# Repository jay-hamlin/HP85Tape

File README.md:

PYTHON
 - command line: python3 hp85Main.py
 - edit hp85Uart.py with path of FTDI serial port.

FPGA
 - FPGA is Lattice iCE40HX1K-TQ144
 - Use Lattice ICEStick development board.
 - Editor is MS Visual Studio Code
 - Simulation with Mentor Graphics ModelSim "PE Student Edition"
 - Synthesis with LAttice iCECube2. Use Synplify Pro option.
 - Program FPGA with Lattice Diamond Programmer.

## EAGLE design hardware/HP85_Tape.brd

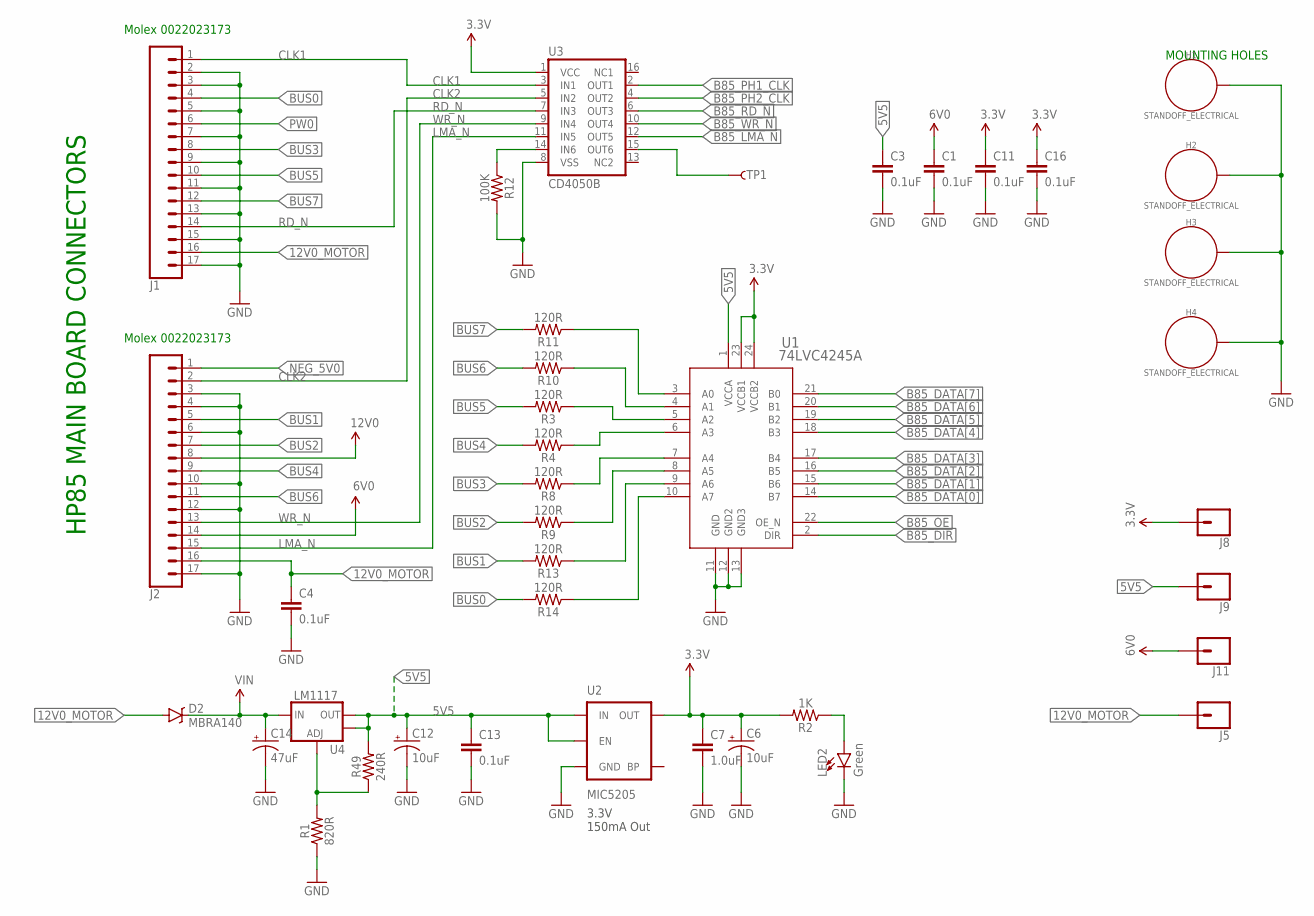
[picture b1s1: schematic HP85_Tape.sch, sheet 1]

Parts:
C1, C3, C4, C11, C13, C16: 0.1uF; 0603
C6, C12: 10uF; EIA3216
C7: 1.0uF; 0603
C14: 47uF; PANASONIC_D
D2: MBRA140; SMA-DIODE
H1, H2, H3, H4: STANDOFF_ELECTRICAL; STANDOFF-ELECTRICAL
J1, J2: CONN_17; 1X17
J5, J8, J9, J11: CONN_01; 1X01
LED2: Green; LED-1206
R1: 820R; 0603
R2: 1K; 0603
R3, R4, R8, R9, R10, R11, R13, R14: 120R; 0603
R12: 100K; 0603
R49: 240R; 0603
TP1: TP-3x5; PAD.03X.05
U1: 74LVC4245A; SO-24-M
U2: MIC5205; SOT23-5
U3: CD4050B; SO16
U4: LM1117; SOT223-ALT1

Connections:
3.3V: C6.+, C7.1, C11.1, C16.1, J8.1, R2.2, U1.23 (VCCB1), U1.24 (VCCB2), U2.5 (OUT), U3.1 (VCC); also elsewhere on the board
5V5: C3.1, C12.+, C13.1, J9.1, R49.2, U1.1 (VCCA), U2.1 (IN), U2.3 (EN), U4.2 (OUT), U4.4 (OUT)
6V0: C1.1, J2.14, J11.1
12V0: J2.8
12V0_MOTOR: C4.1, D2.A, J1.16, J2.16, J5.1
B85_DATA[0]: U1.14 (B7); also elsewhere on the board
B85_DATA[1]: U1.15 (B6); also elsewhere on the board
B85_DATA[2]: U1.16 (B5); also elsewhere on the board
B85_DATA[3]: U1.17 (B4); also elsewhere on the board
B85_DATA[4]: U1.18 (B3); also elsewhere on the board
B85_DATA[5]: U1.19 (B2); also elsewhere on the board
B85_DATA[6]: U1.20 (B1); also elsewhere on the board
B85_DATA[7]: U1.21 (B0); also elsewhere on the board
B85_DIR: U1.2 (DIR); also elsewhere on the board
B85_LMA_N: U3.12 (OUT5); also elsewhere on the board
B85_OE: U1.22 (OE_N); also elsewhere on the board
B85_PH1_CLK: U3.2 (OUT1); also elsewhere on the board
B85_PH2_CLK: U3.4 (OUT2); also elsewhere on the board
B85_RD_N: U3.6 (OUT3); also elsewhere on the board
B85_WR_N: U3.10 (OUT4); also elsewhere on the board
BUS0: J1.4, R14.2
BUS1: J2.5, R13.2
BUS2: J2.7, R9.2
BUS3: J1.8, R8.2
BUS4: J2.9, R4.2
BUS5: J1.10, R3.2
BUS6: J2.11, R10.2
BUS7: J1.12, R11.2
CLK1: J1.1, U3.3 (IN1)
CLK2: J2.2, U3.5 (IN2)
GND: C1.2, C3.2, C4.2, C6.-, C7.2, C11.2, C12.-, C13.2, C14.-, C16.2, H1.P1, H2.P1, H3.P1, H4.P1, J1.2, J1.3, J1.5, J1.7, J1.9, J1.11, J1.13, J1.15, J1.17, J2.3, J2.4, J2.6, J2.10, J2.12, J2.17, LED2.C, R1.1, R12.2, U1.11 (GND), U1.12 (GND2), U1.13 (GND3), U2.2 (GND), U3.8 (VSS); also elsewhere on the board
LMA_N: J2.15, U3.11 (IN5)
unnamed: LED2.A, R2.1
unnamed: R1.2, R49.1, U4.1 (ADJ)
unnamed: R12.1, U3.14 (IN6)
unnamed: R14.1, U1.10 (A7)
unnamed: TP1.P$1, U3.15 (OUT6)
unnamed: R13.1, U1.9 (A6)
unnamed: R9.1, U1.8 (A5)
unnamed: R8.1, U1.7 (A4)
unnamed: R4.1, U1.6 (A3)
unnamed: R3.1, U1.5 (A2)
unnamed: R10.1, U1.4 (A1)
unnamed: R11.1, U1.3 (A0)
NEG_5V0: J2.1
PW0: J1.6
RD_N: J1.14, U3.7 (IN3)
VIN: C14.+, D2.C, U4.3 (IN)
WR_N: J2.13, U3.9 (IN4)

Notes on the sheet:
3.3V 150mA Out
HP85 MAIN BOARD CONNECTORS
MOUNTING HOLES
Molex 0022023173

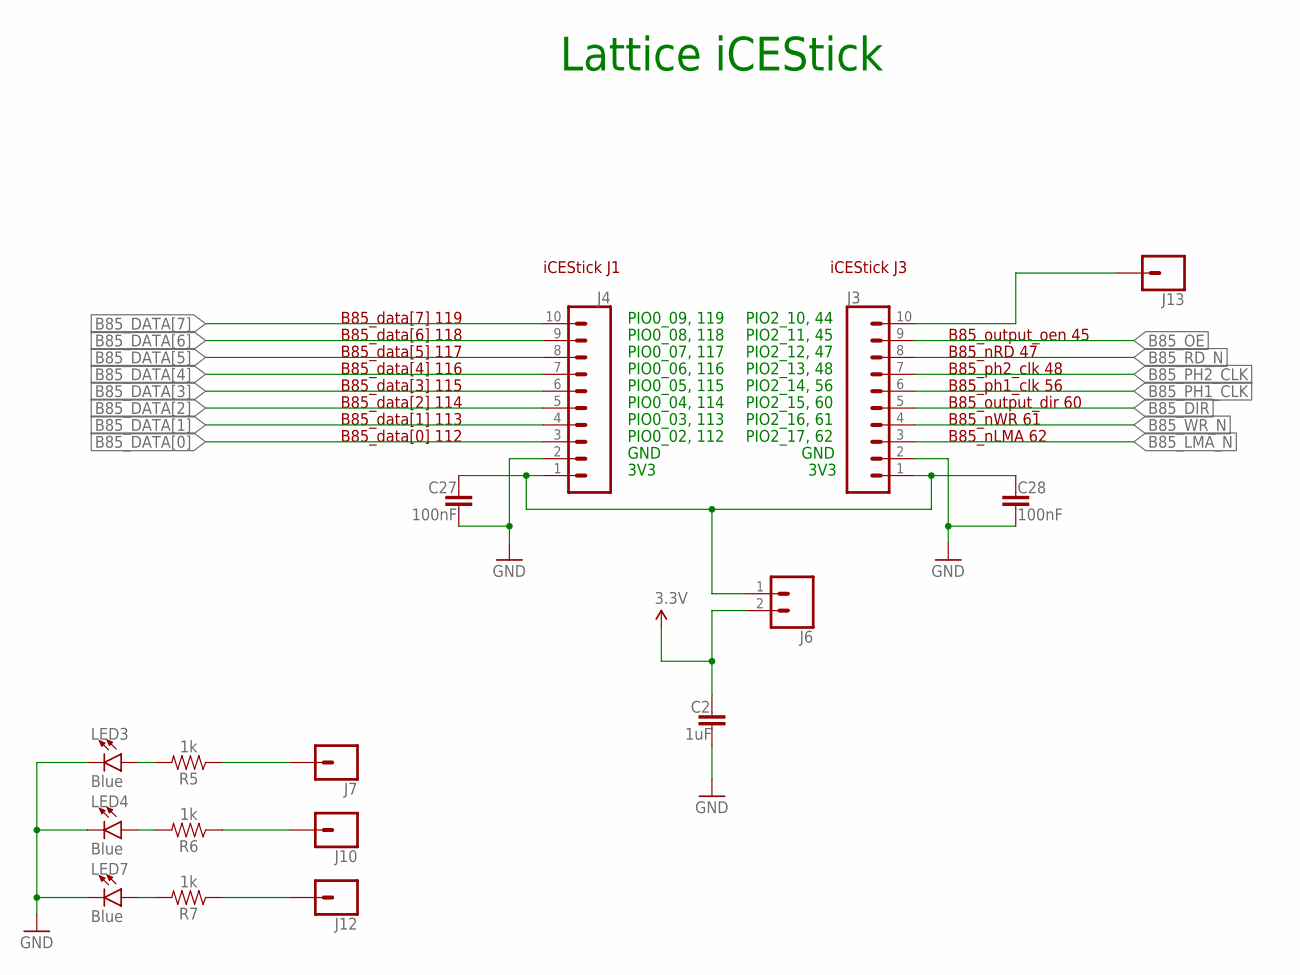
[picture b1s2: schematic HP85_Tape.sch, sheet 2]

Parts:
C2: 1uF; 0603
C27, C28: 100nF; 0603
J3, J4: CONN_10"; 1X10
J6: CONN_02; 1X02
J7, J10, J12, J13: CONN_01; 1X01
LED3, LED4, LED7: Blue; LED-1206
R5, R6, R7: 1k; 0603

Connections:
3.3V: C2.1, J6.2; also elsewhere on the board
B85_DATA[0]: J4.3; also elsewhere on the board
B85_DATA[1]: J4.4; also elsewhere on the board
B85_DATA[2]: J4.5; also elsewhere on the board
B85_DATA[3]: J4.6; also elsewhere on the board
B85_DATA[4]: J4.7; also elsewhere on the board
B85_DATA[5]: J4.8; also elsewhere on the board
B85_DATA[6]: J4.9; also elsewhere on the board
B85_DATA[7]: J4.10; also elsewhere on the board
B85_DIR: J3.5; also elsewhere on the board
B85_LMA_N: J3.3; also elsewhere on the board
B85_OE: J3.9; also elsewhere on the board
B85_PH1_CLK: J3.6; also elsewhere on the board
B85_PH2_CLK: J3.7; also elsewhere on the board
B85_RD_N: J3.8; also elsewhere on the board
B85_WR_N: J3.4; also elsewhere on the board
GND: C2.2, C27.2, C28.2, J3.2, J4.2, LED3.C, LED4.C, LED7.C; also elsewhere on the board
unnamed: LED3.A, R5.2
unnamed: LED4.A, R6.2
unnamed: LED7.A, R7.2
unnamed: J12.1, R7.1
unnamed: C27.1, C28.1, J3.1, J4.1, J6.1
unnamed: J10.1, R6.1
unnamed: J7.1, R5.1
unnamed: J3.10, J13.1

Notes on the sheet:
Lattice iCEStick
3V3
GND
PIO0_02, 112
PIO0_03, 113
PIO0_04, 114
PIO0_05, 115
PIO0_06, 116
PIO0_07, 117
PIO0_08, 118
PIO0_09, 119
PIO2_10, 44
PIO2_11, 45
PIO2_12, 47
PIO2_13, 48
PIO2_14, 56
PIO2_15, 60
PIO2_16, 61
PIO2_17, 62
iCEStick J1
iCEStick J3
B85_data[7] 119
B85_nLMA 62
B85_nWR 61
B85_data[6] 118
B85_data[1] 113
B85_data[5] 117
B85_ph1_clk 56
B85_data[0] 112
B85_data[4] 116
B85_output_dir 60
B85_data[3] 115
B85_ph2_clk 48
B85_data[2] 114
B85_output_oen 45
B85_nRD 47

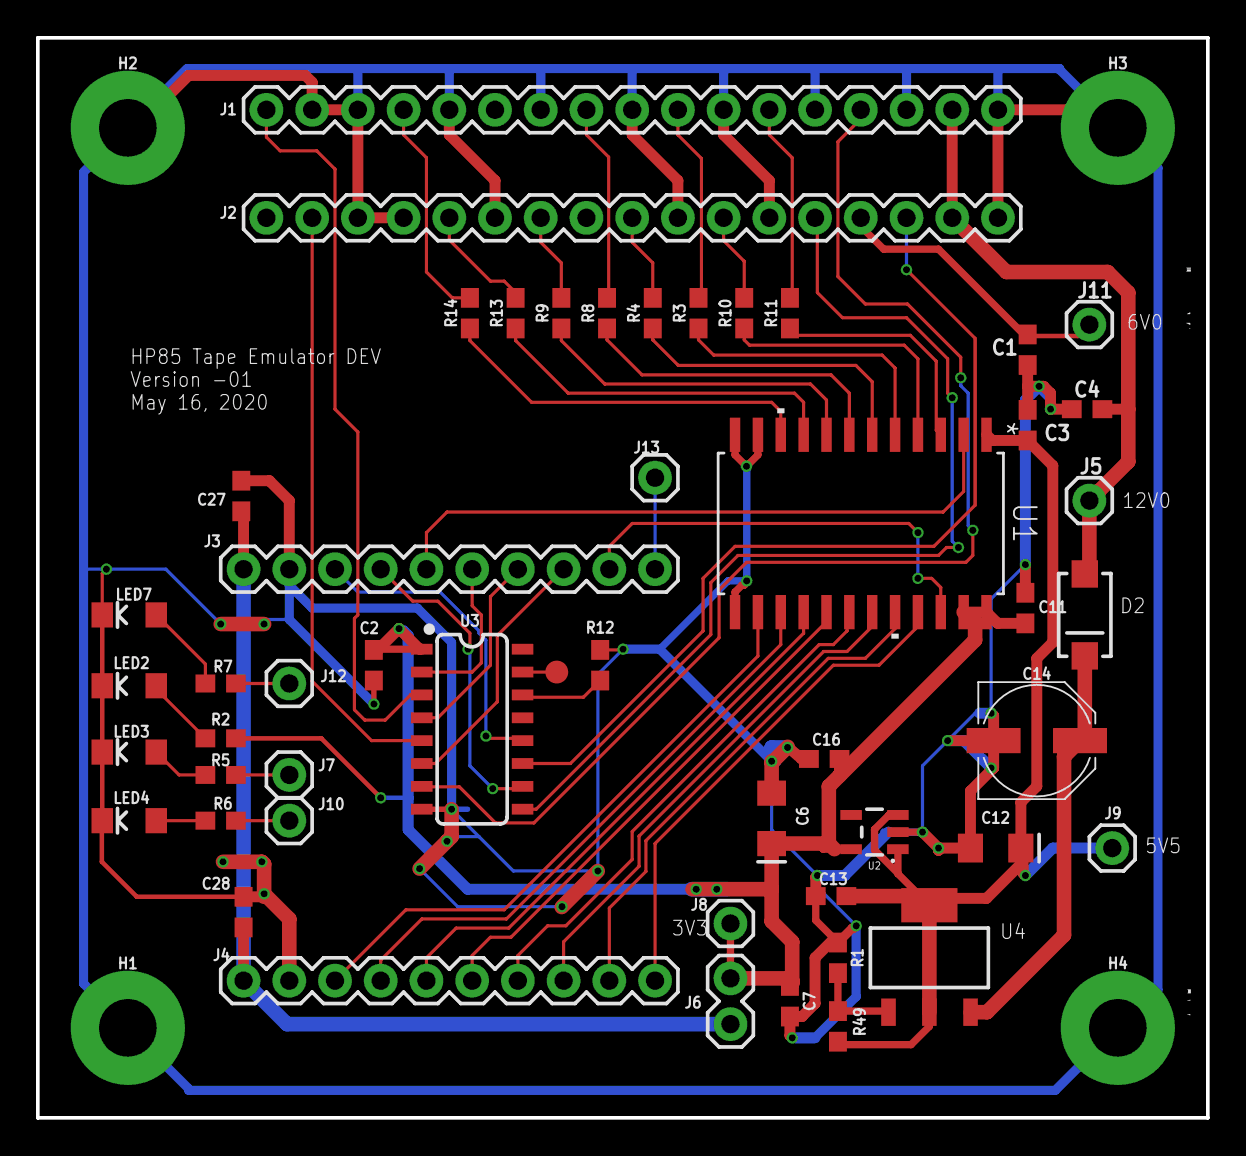
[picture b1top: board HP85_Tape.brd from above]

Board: 2 copper layers, 65.0 x 60.0 mm, 55 parts (0 on the bottom side), 54 nets.

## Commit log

2020-06-10 Project setup
2020-06-10 fixed hdr bug, header
2020-06-11 added transport
2020-06-15 added protocol HOLE commands and fixed tachometer timing
2020-06-17 added hole command
2020-06-17 updating python
2020-06-18 REWIND is working
2020-06-18 pyserial debugging
2020-06-23 adding some documentation

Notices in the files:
parts and their libraries:
SparkFun-Connectors: Licensing: CC v3.0 Share-Alike You are welcome to use this library for commercial purposes.
SparkFun-PowerIC: Licensing: Creative Commons ShareAlike 4.0 International - https://creativecommons.org/licenses/by-sa/4.0
